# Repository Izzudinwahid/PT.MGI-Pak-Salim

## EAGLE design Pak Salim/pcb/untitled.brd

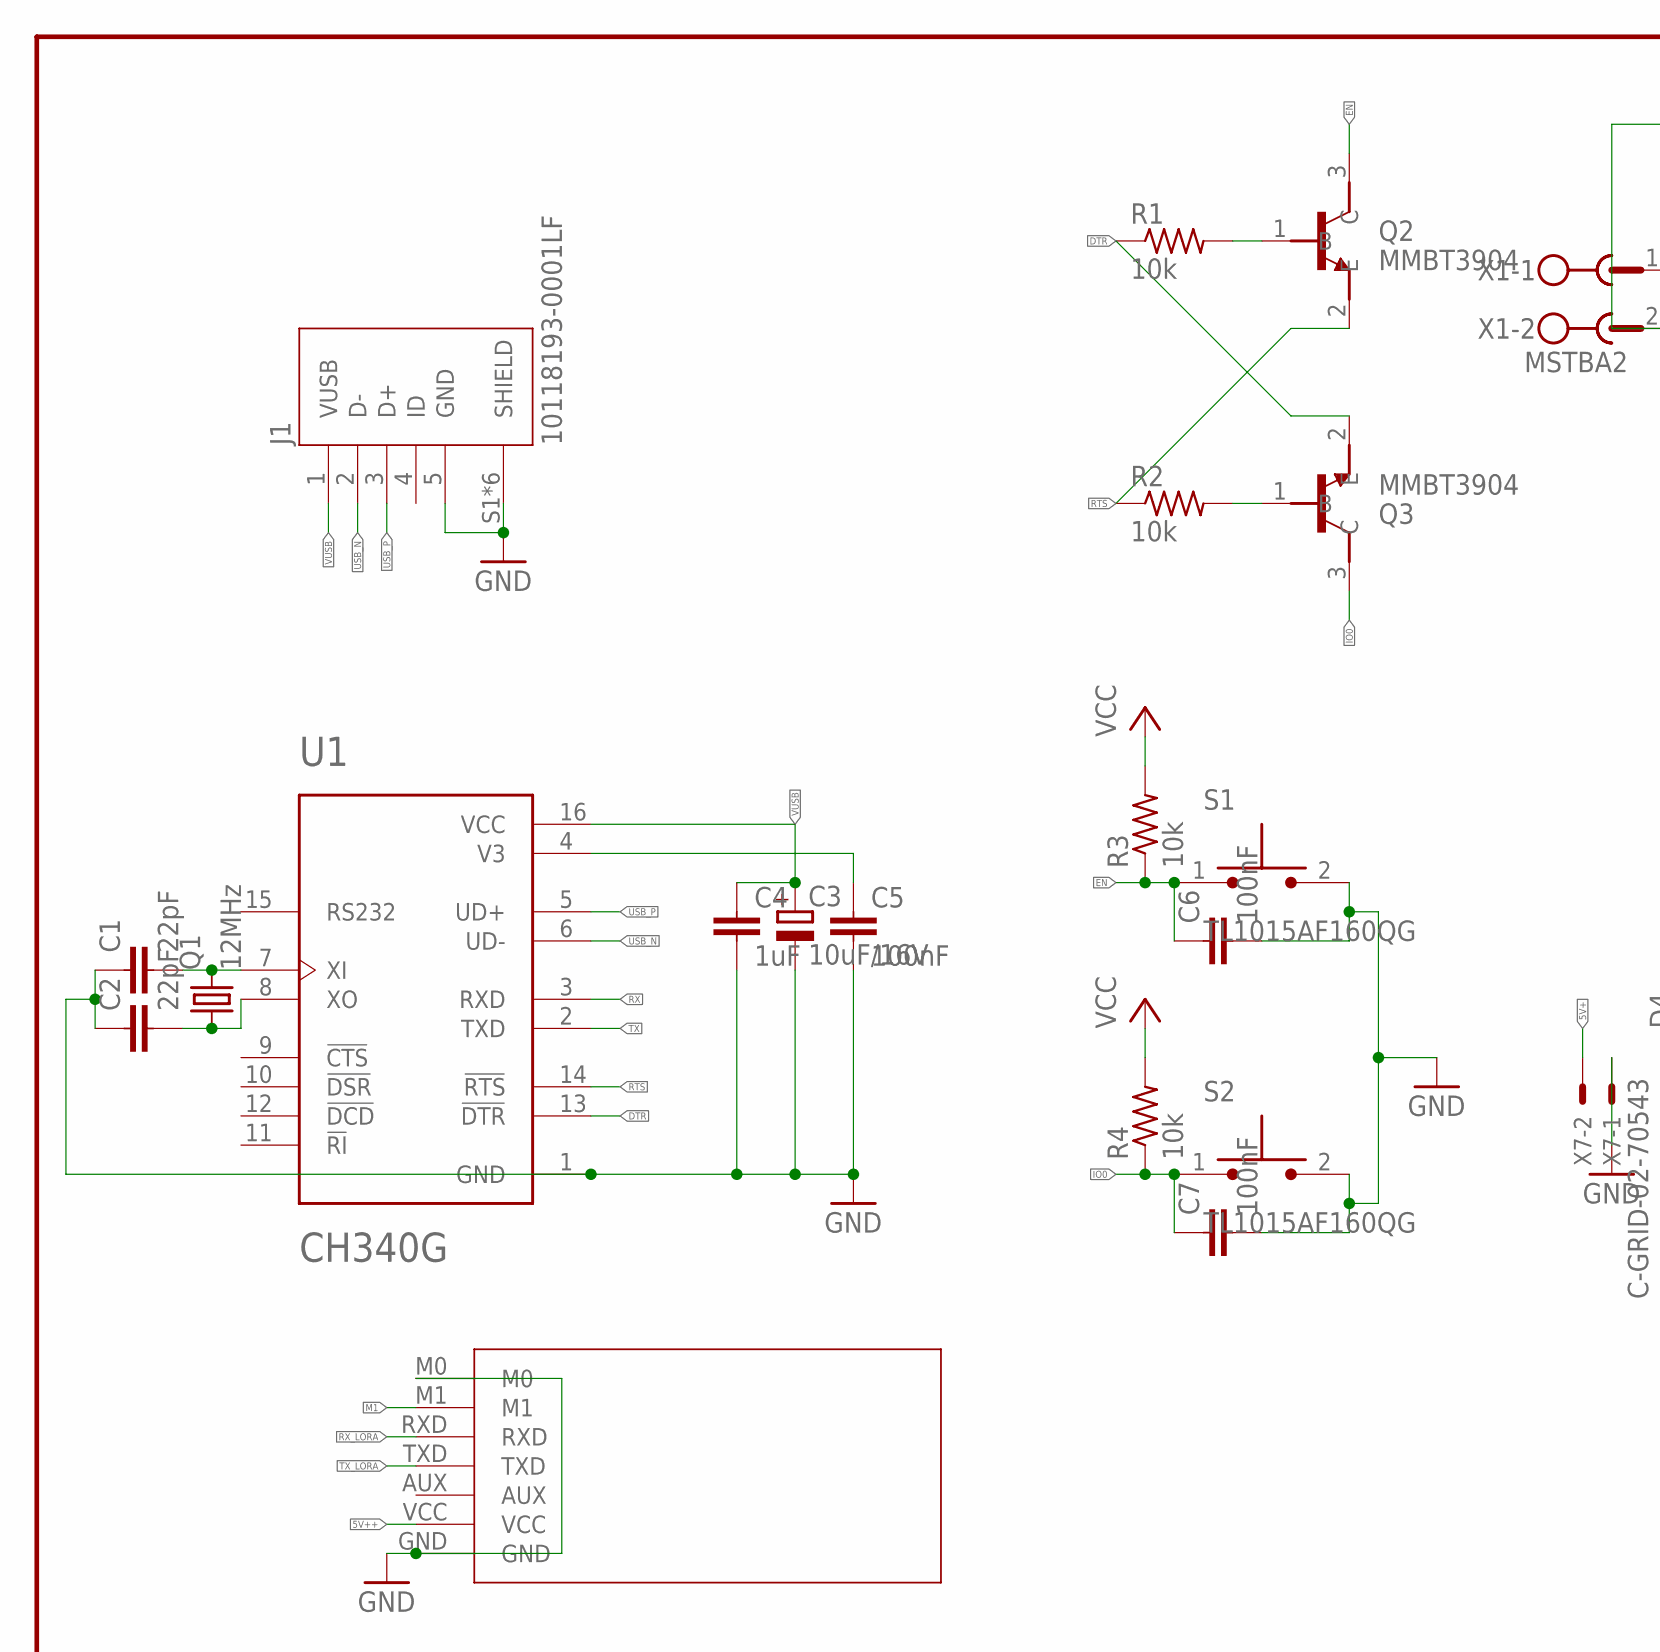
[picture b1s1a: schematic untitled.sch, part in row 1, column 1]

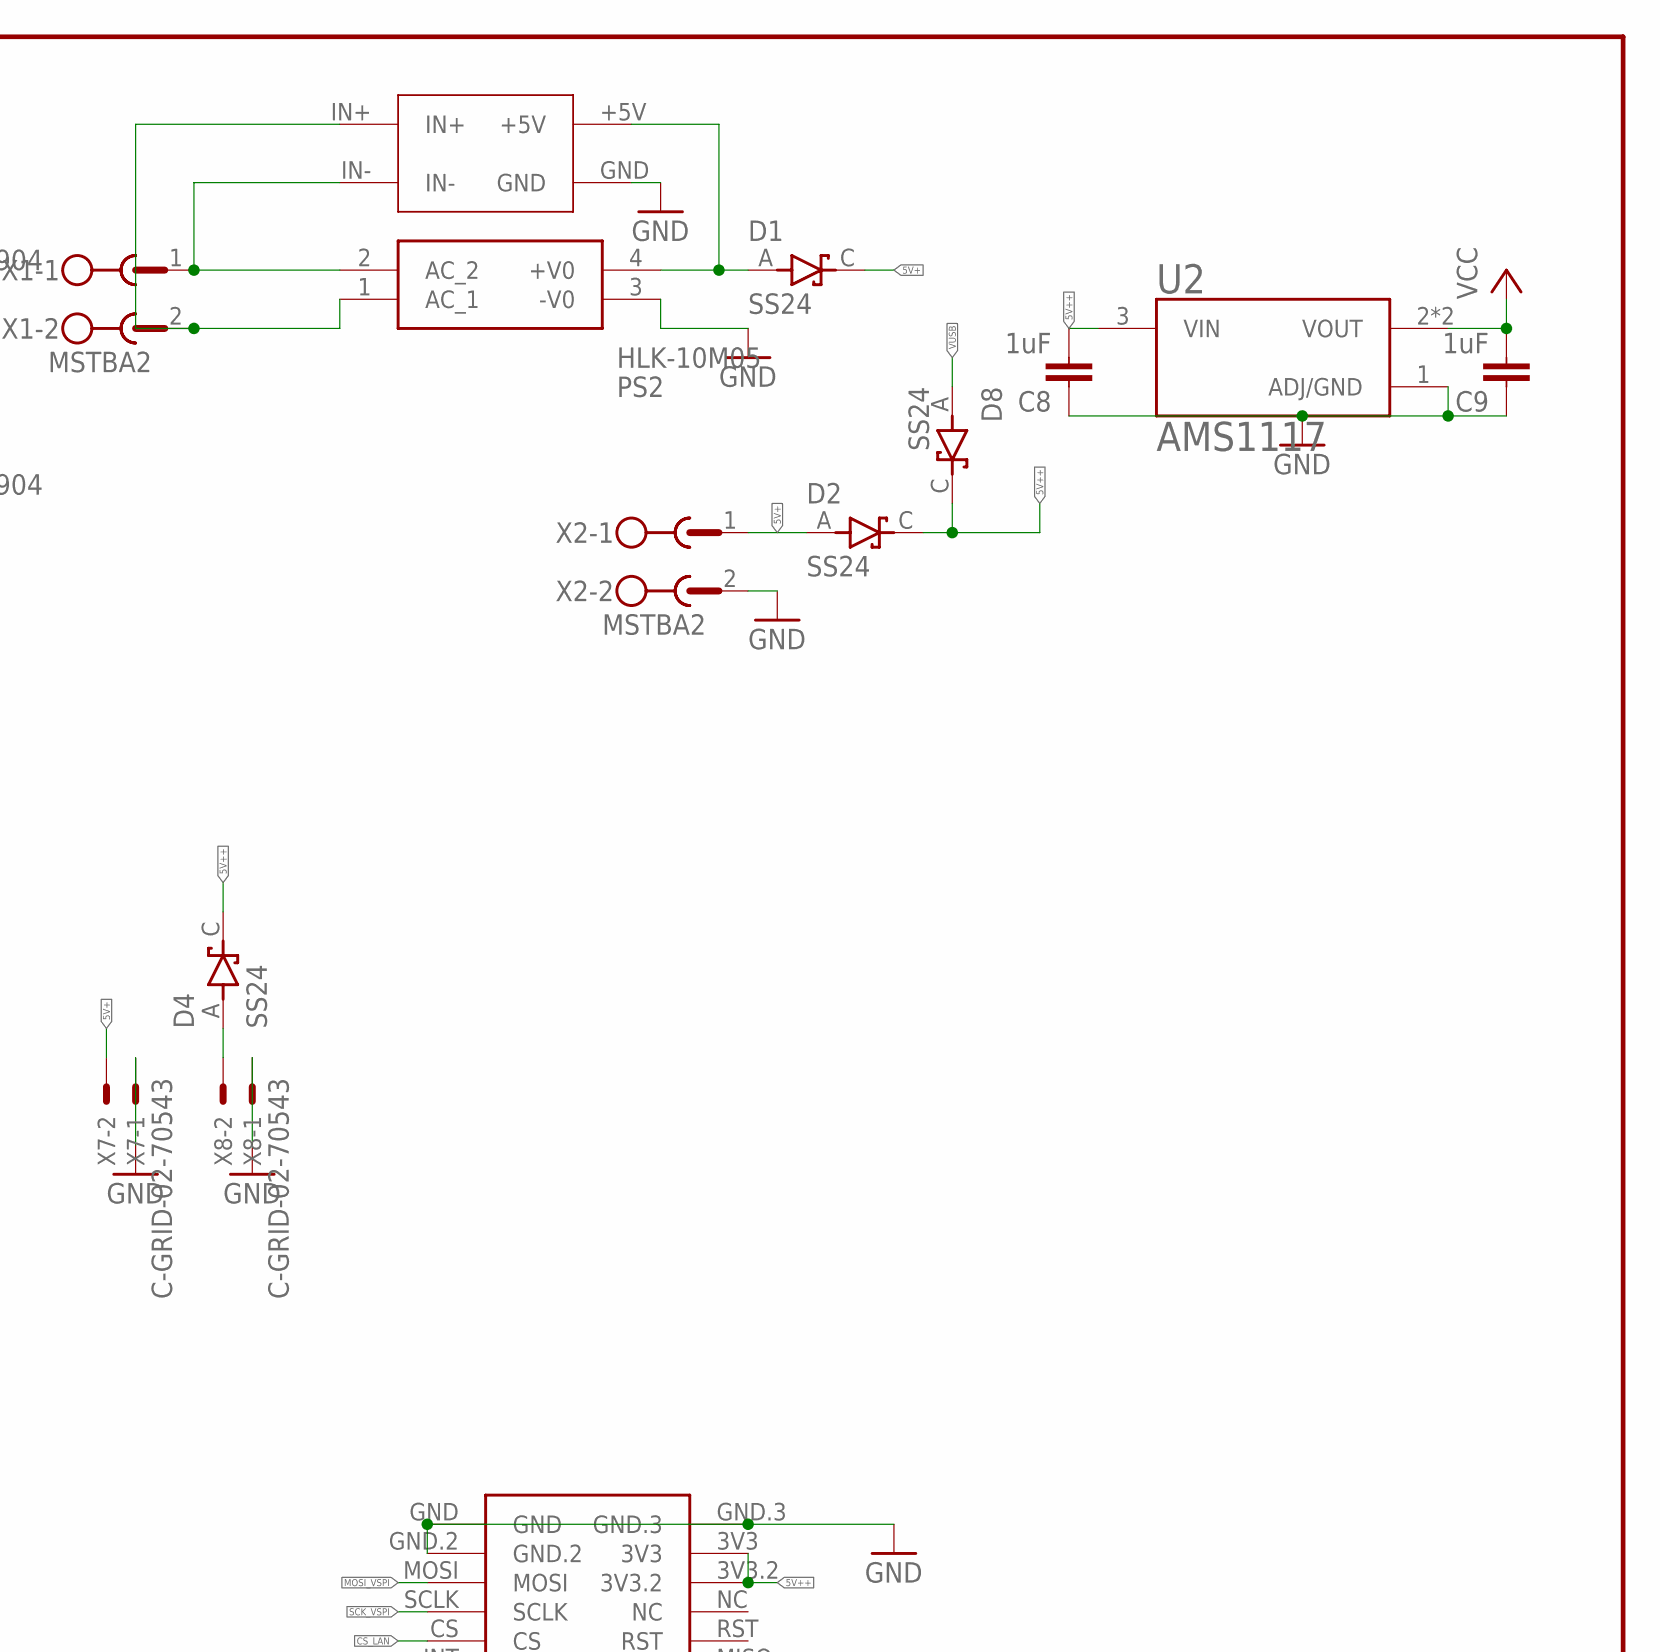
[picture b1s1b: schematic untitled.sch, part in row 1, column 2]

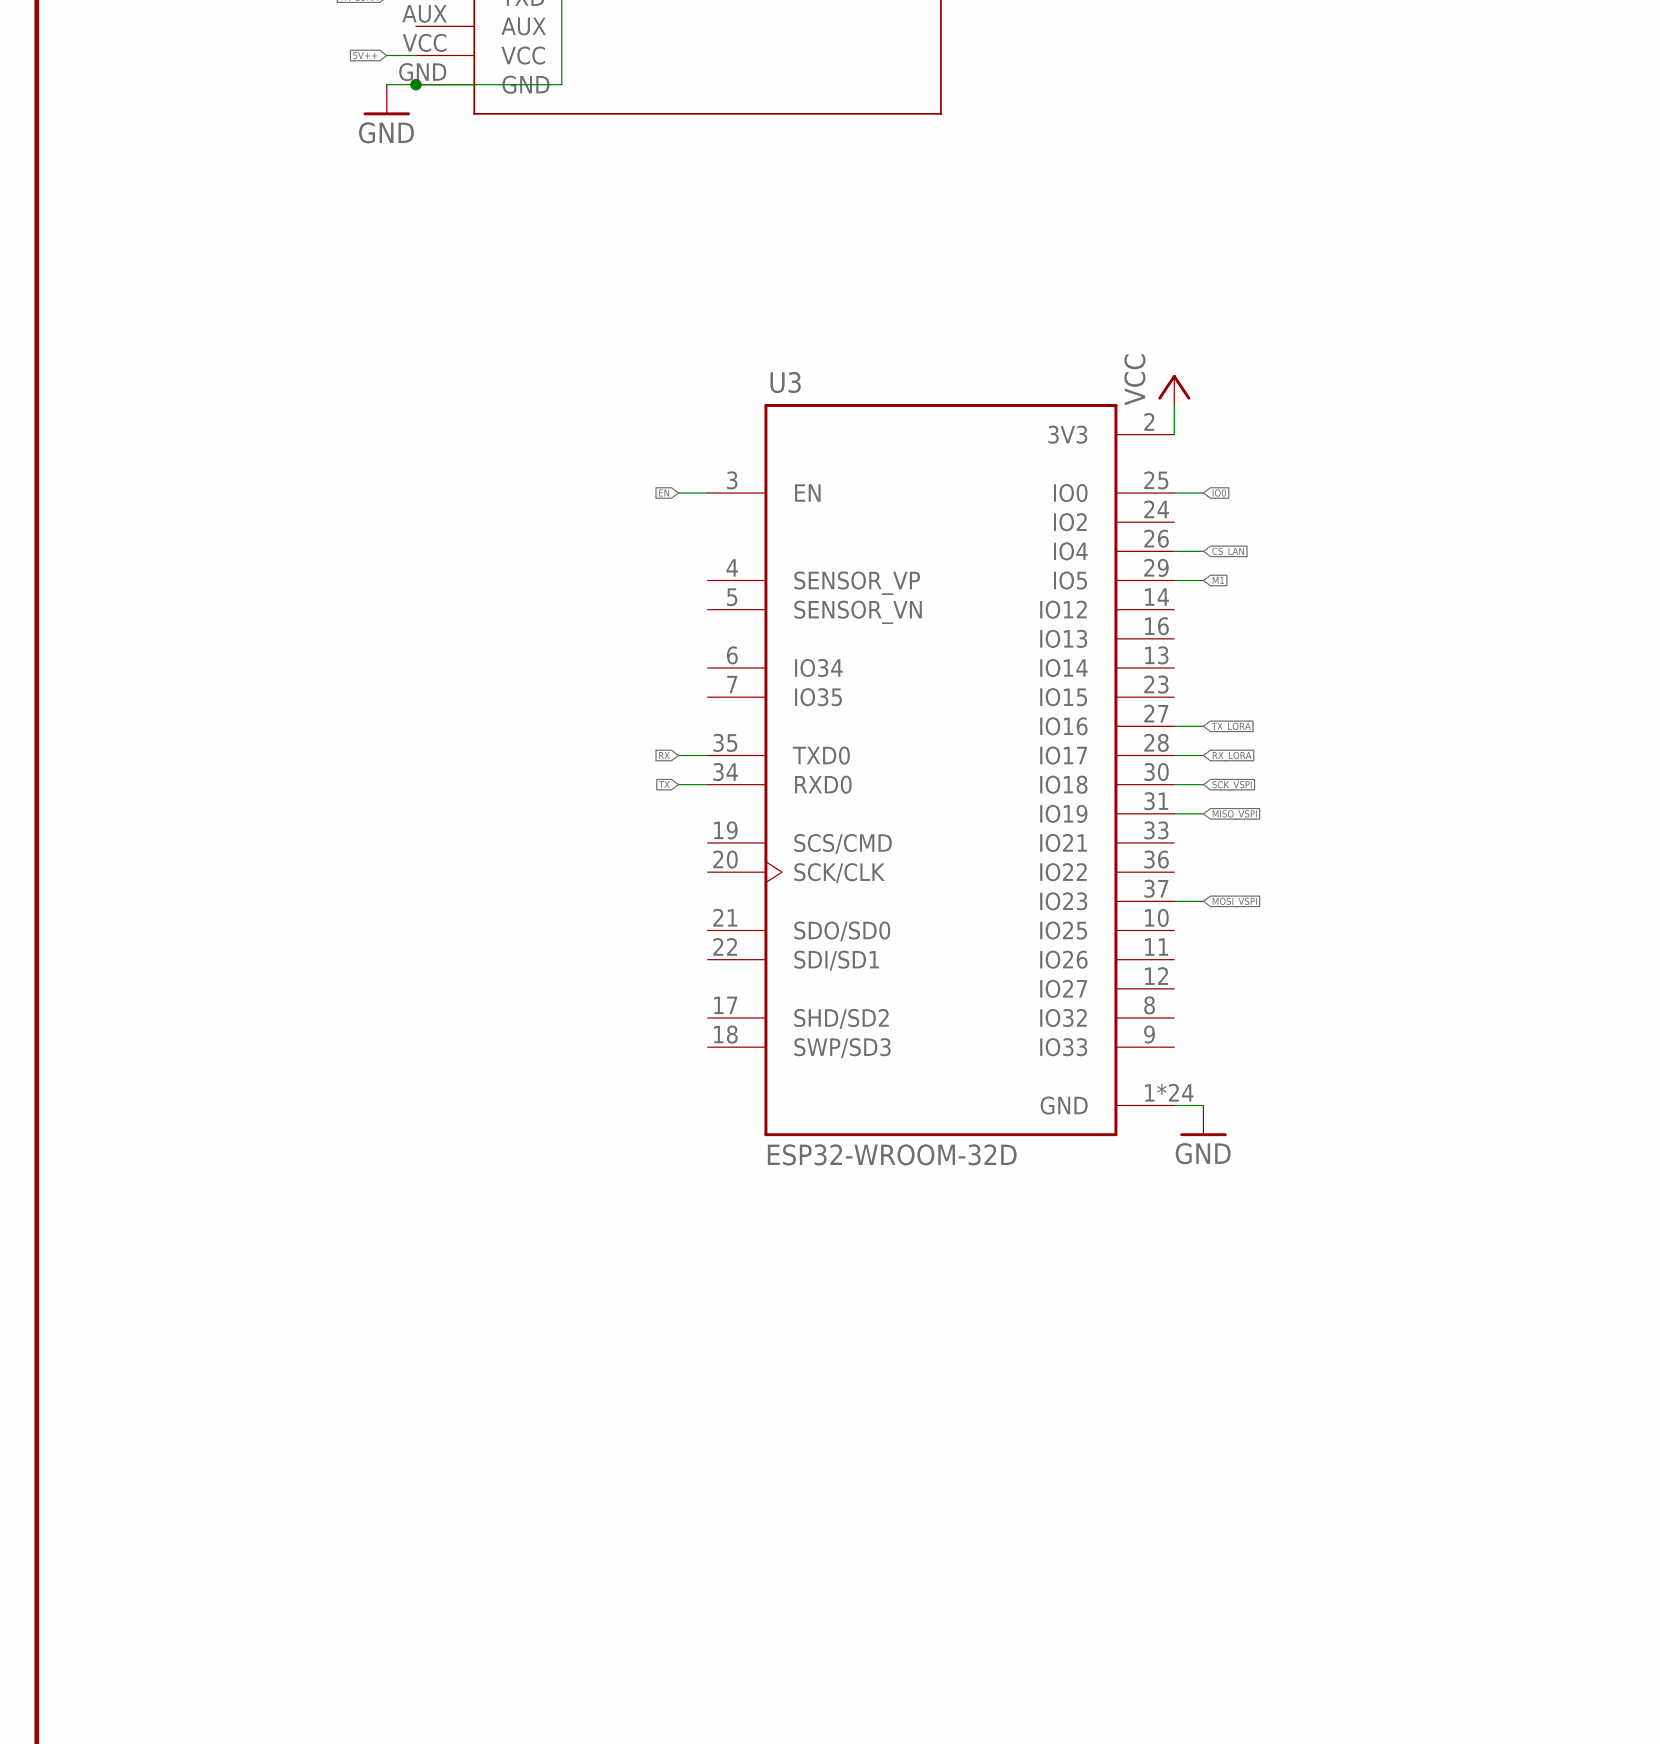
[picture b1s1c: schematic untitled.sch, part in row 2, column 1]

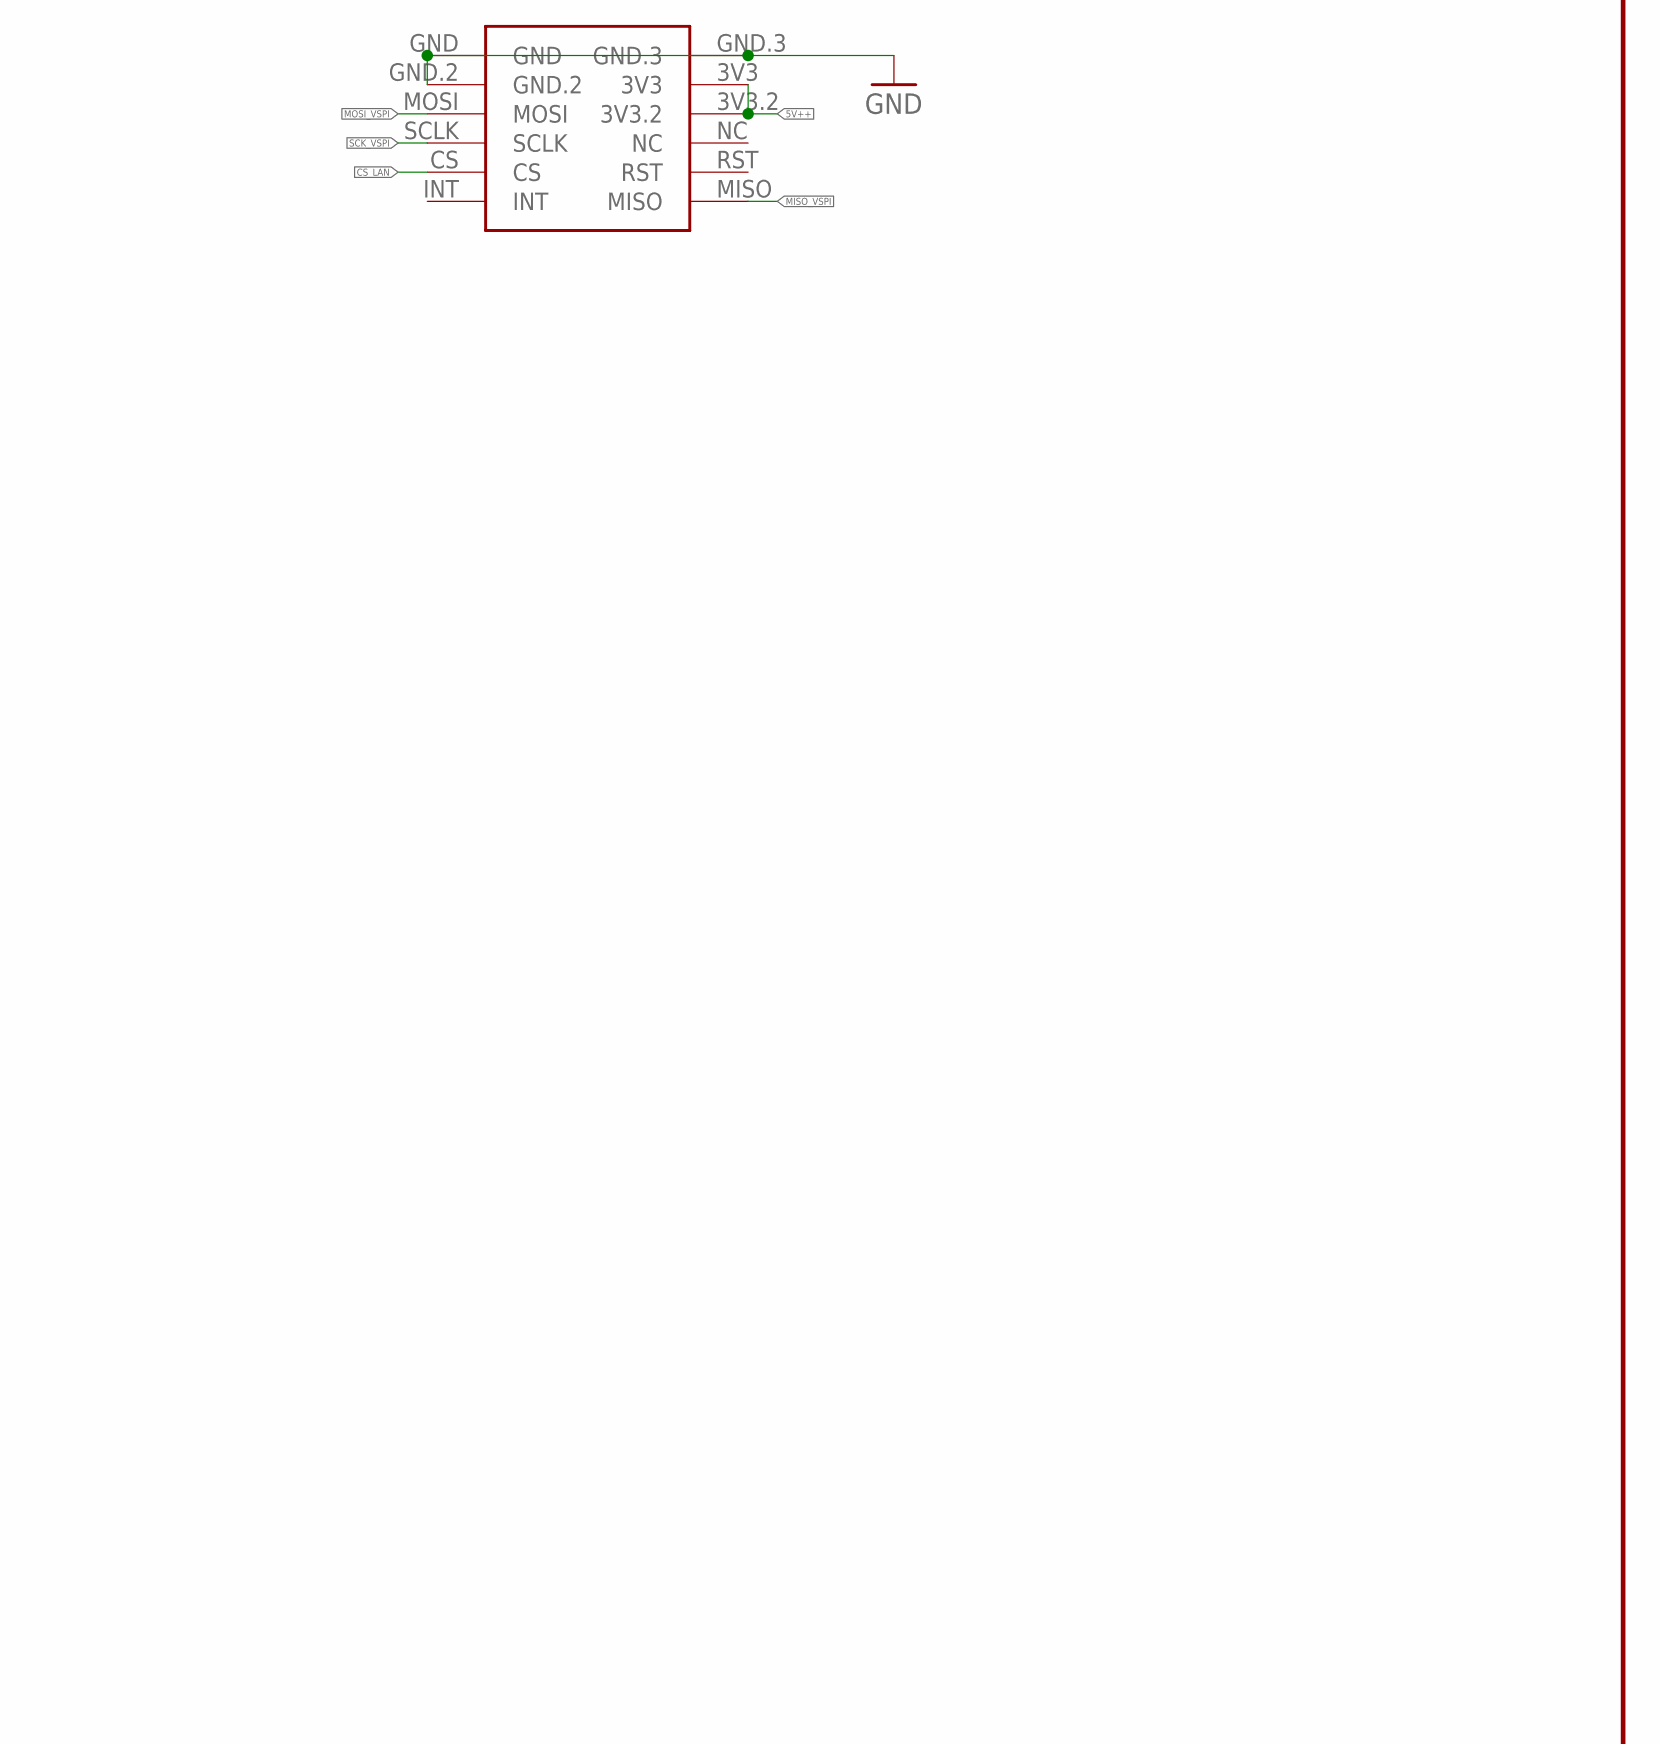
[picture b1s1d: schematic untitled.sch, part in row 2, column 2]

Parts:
C1, C2: 22pF; C0805K
C3: 10uF/16V; 153CLV-0505
C4, C8, C9: 1uF; C0805K
C5, C6, C7: 100nF; C0805K
D1, D2, D4, D8: SS24; DIOM5336X265N
EBYTEE220-900T22D1: EBYTEE220-900T22D
J1: 10118193-0001LF; FCI_10118193-0001LF
PS2: HLK-10M05; HLK10M05
Q1: 12MHz; SM49
Q2, Q3: MMBT3904; SOT95P240X120-3N
R1, R2, R3, R4: 10k; M0805
S1, S2: TL1015AF160QG; SW_TL1015AF160QG
SUPER-STEPDOWN1: SUPER-STEPDOWN
U1: CH340G; SOIC127P600X180-16N
U2: AMS1117; SOT229P700X180-4N
U3: ESP32-WROOM-32D; MODULE_ESP32-WROOM-32D
U$1: MINI_W5500
X1, X2: MSTBA2
X7, X8: C-GRID-02-70543; 70543-02

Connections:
5V+: D1.C (K), D2.A, X2.1, X7.2
5V++: C8.2, D2.C (K), D4.C (K), D8.C (K), EBYTEE220-900T22D1.VCC, U2.3 (VIN), U$1.3V3, U$1.3V3.2
CS_LAN: U3.26 (IO4), U$1.CS
DTR: Q3.2 (E), R1.1, U1.13 (!DTR)
EN: C6.1, Q2.3 (C), R3.1, S1.1, U3.3 (EN)
GND(VERSION1): C1.1, C2.1, C3.-, C4.2, C5.2, C6.2, C7.2, C8.1, C9.1, EBYTEE220-900T22D1.GND, EBYTEE220-900T22D1.M0, J1.5 (GND), J1.S1 (SHIELD), J1.S2 (SHIELD), J1.S3 (SHIELD), J1.S4 (SHIELD), J1.S5 (SHIELD), J1.S6 (SHIELD), PS2.3 (-V0), S1.2, S2.2, SUPER-STEPDOWN1.GND, U1.1 (GND), U2.1 (ADJ/GND), U3.1 (GND), U3.15 (GND), U3.38 (GND), U3.39_1 (GND), U3.39_2 (GND), U3.39_3 (GND), U3.39_4 (GND), U3.39_5 (GND), U3.39_6 (GND), U3.39_7 (GND), U3.39_8 (GND), U3.39_9 (GND), U3.39_10 (GND), U3.39_11 (GND), U3.39_12 (GND), U3.39_13 (GND), U3.39_14 (GND), U3.39_15 (GND), U3.39_16 (GND), U3.39_17 (GND), U3.39_18 (GND), U3.39_19 (GND), U3.39_20 (GND), U3.39_21 (GND), U$1.GND, U$1.GND.2, U$1.GND.3, X2.2, X7.1, X8.1
IO0: C7.1, Q3.3 (C), R4.1, S2.1, U3.25 (IO0)
M1: EBYTEE220-900T22D1.M1, U3.29 (IO5)
MISO_VSPI: U3.31 (IO19), U$1.MISO
MOSI_VSPI: U3.37 (IO23), U$1.MOSI
unnamed: PS2.2 (AC_2), SUPER-STEPDOWN1.IN-, X1.1
unnamed: C5.1, U1.4 (V3)
unnamed: Q2.1 (B), R1.2
unnamed: C1.2, Q1.2, U1.7 (XI)
unnamed: C2.2, Q1.1, U1.8 (XO)
unnamed: Q3.1 (B), R2.2
unnamed: PS2.1 (AC_1), SUPER-STEPDOWN1.IN+, X1.2
unnamed: D1.A, PS2.4 (+V0), SUPER-STEPDOWN1.+5V
unnamed: D4.A, X8.2
RTS: Q2.2 (E), R2.1, U1.14 (!RTS)
RX: U1.3 (RXD), U3.35 (TXD0)
RX_LORA: EBYTEE220-900T22D1.RXD, U3.28 (IO17)
SCK_VSPI: U3.30 (IO18), U$1.SCLK
TX: U1.2 (TXD), U3.34 (RXD0)
TX_LORA: EBYTEE220-900T22D1.TXD, U3.27 (IO16)
USB_N: J1.2 (D-), U1.6 (UD-)
USB_P: J1.3 (D+), U1.5 (UD+)
VCC: C9.2, R3.2, R4.2, U2.2 (VOUT), U2.4 (VOUT), U3.2 (3V3)
VUSB: C3.+, C4.1, D8.A, J1.1 (VUSB), U1.16 (VCC)

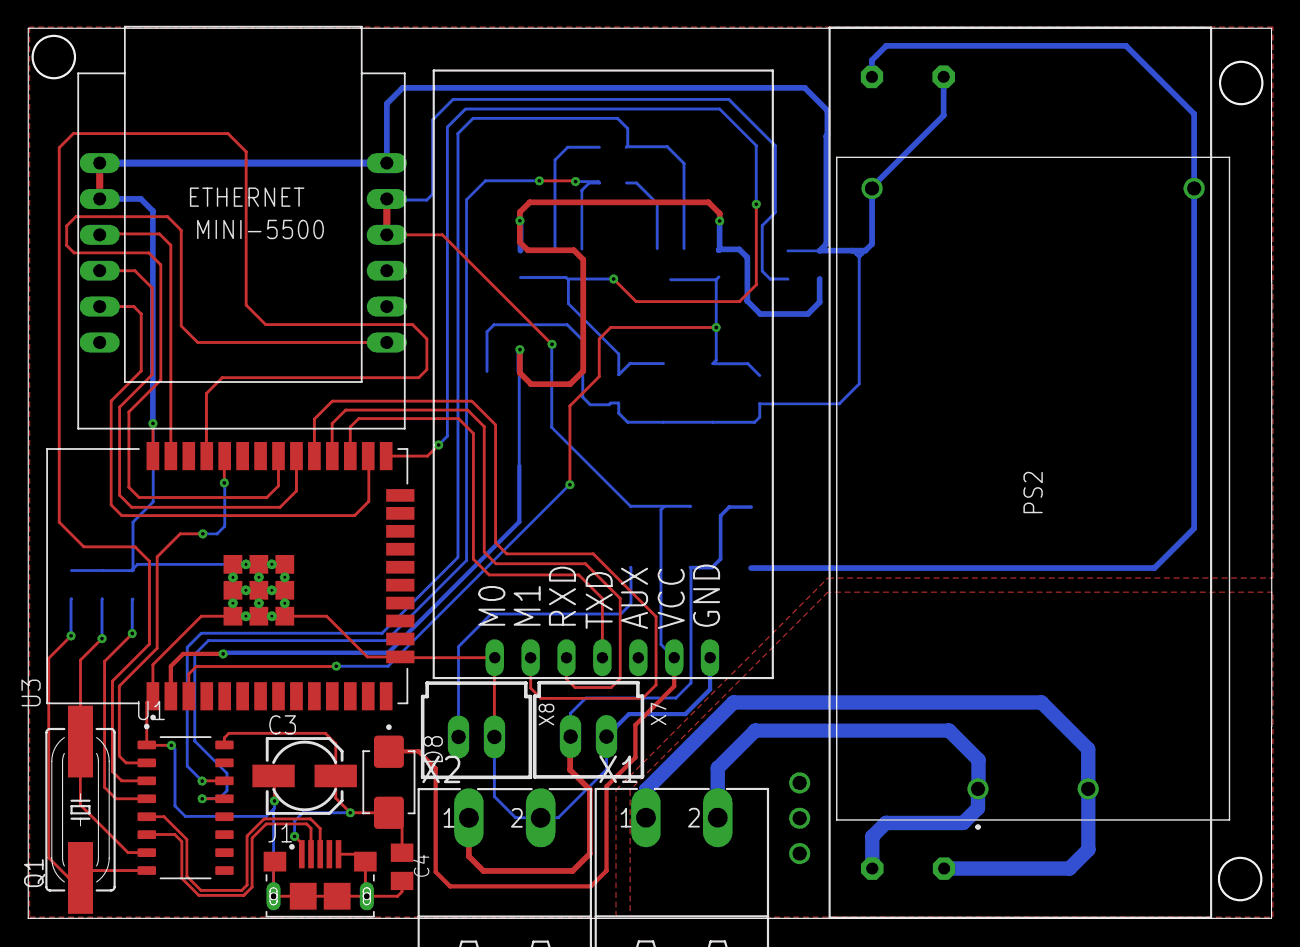
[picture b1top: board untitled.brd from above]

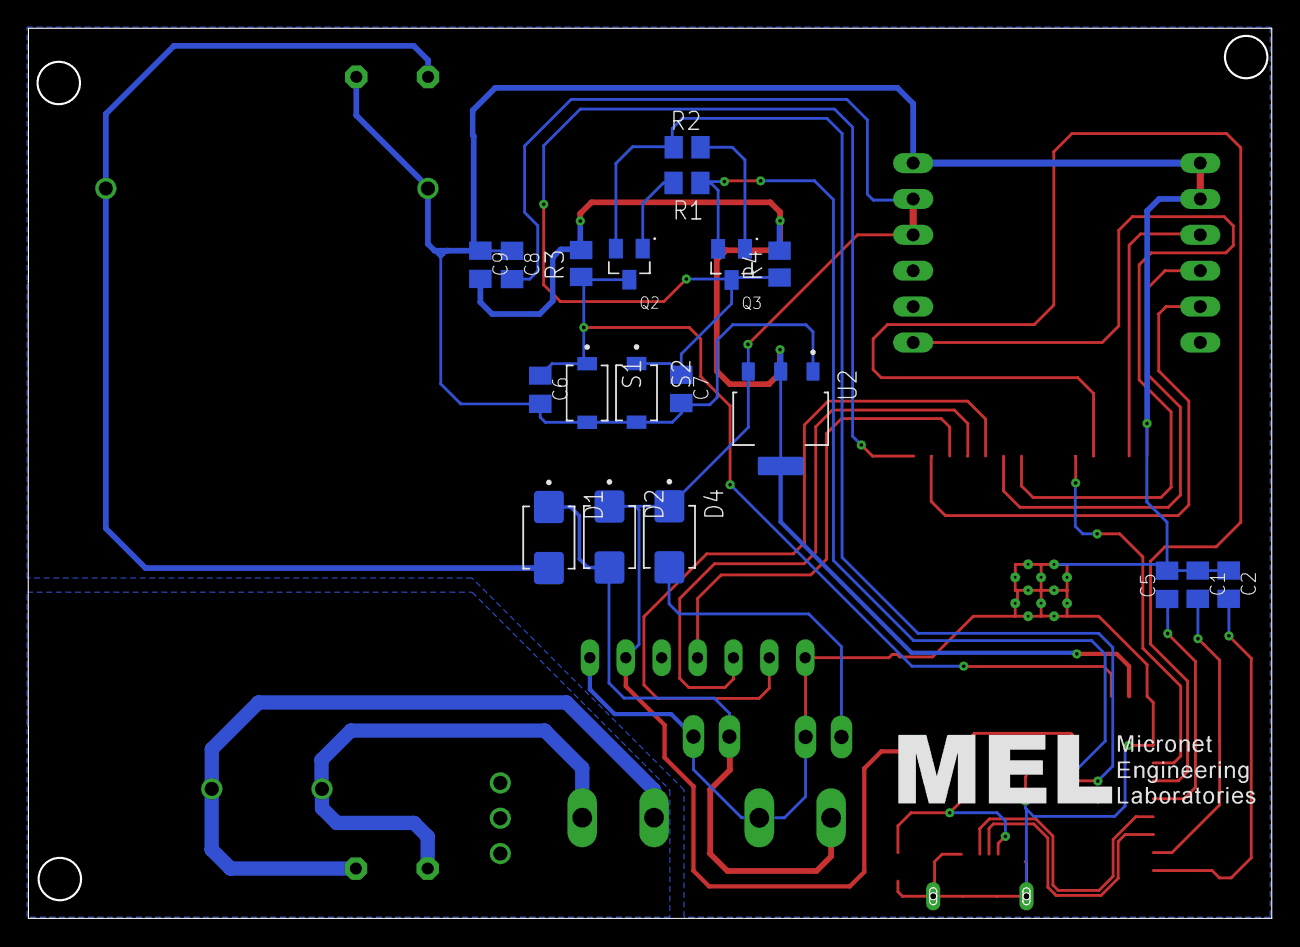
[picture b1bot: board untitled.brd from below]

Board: 2 copper layers, 88.0 x 63.0 mm, 34 parts (19 on the bottom side), 29 nets.

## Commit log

2024-08-09 PCB v1.0
